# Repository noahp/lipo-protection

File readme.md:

# Single cell lipo protection circuit
Based on the [SII S-8200A](http://www.sii-ic.com/en/semicon/datasheets/power-management-ic/lithium-ion-battery-protection-ic/s-8200a/); datasheet [here](http://datasheet.sii-ic.com/en/battery_protection/S8200A_E.pdf).

Example circuit from datasheet-

# Fet
http://www.digikey.com/product-detail/en/diodes-incorporated/DMG3420U-7/DMG3420U-7DICT-ND/2279223

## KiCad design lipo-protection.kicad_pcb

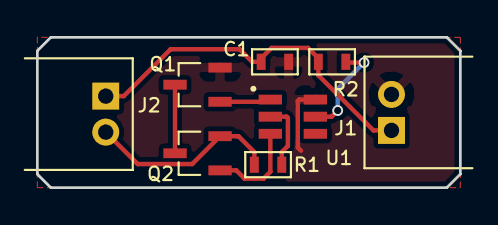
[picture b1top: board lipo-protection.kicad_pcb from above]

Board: 2 copper layers, 23.5 x 8.3 mm, 8 parts (0 on the bottom side), 8 nets.

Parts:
C1: 0.1µF; SMD_0603_C
J1, J2: 2_PIN_HDR; TH_JST_2PIN_RIGHTANGLE
Q1, Q2: Q_NMOS_GSD; SMD_SOT23-3
R1: 2K; SMD_0603_R
R2: 330; SMD_0603_R
U1: S-8200A; SMD_SOT23-6

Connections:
/batt+: C1.1, J1.1, J2.1, R2.1
/power-: J2.2, Q2.2, R1.2
GND: C1.2, J1.2, Q1.2, U1.6
unnamed: Q1.1, U1.1
unnamed: Q1.3, Q2.3
unnamed: Q2.1, U1.3
unnamed: R1.1, U1.2
unnamed: R2.2, U1.5

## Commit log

2016-05-14 add kicadlib
2016-05-14 add readme.
2016-05-14 schematic done
2016-05-14 start layout
2016-05-14 finish layout
2016-05-15 add gerbers
